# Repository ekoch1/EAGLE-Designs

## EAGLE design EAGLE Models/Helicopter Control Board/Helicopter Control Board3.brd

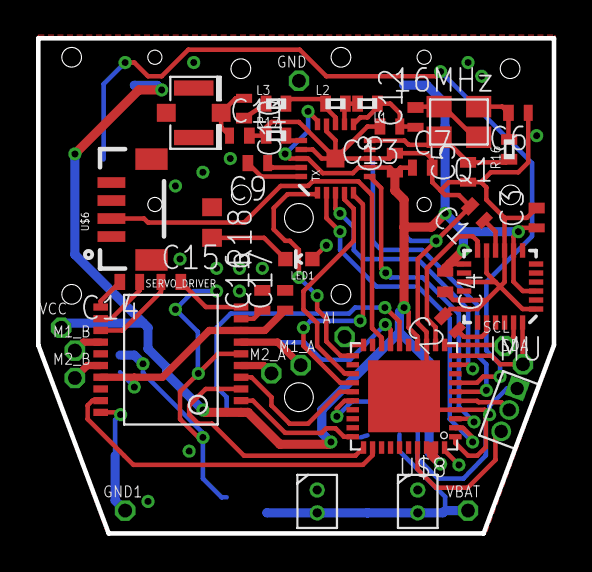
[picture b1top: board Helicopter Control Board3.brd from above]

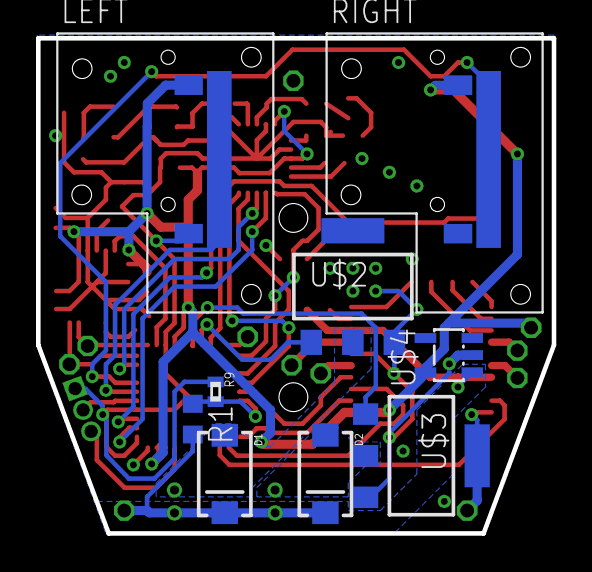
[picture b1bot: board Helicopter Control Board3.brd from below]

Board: 2 copper layers, 28.7 x 27.5 mm, 54 parts (9 on the bottom side), 49 nets.

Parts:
AI: LSP10
C1, C3, C14, C15, C16, C17: .1uF; C0402
C2, C12: 2.2nF; C0402
C4, C8: 10nF; C0402
C5, C6: 22pF; C0402
C7: 1nF; C0402
C9: 33nF; C0402
C10: 1.5pF; C0402
C11: 1pF; C0402
C13: 4.7pF; C0402
D1, D2: SMA-DIODE
GND, GND1: LSP10
IMU: QFN-24-NP
J2: U.FL
L1: 2.7nH; R0402
L2: 8.2nH; R0402
L3: 3.9nH; R0402
LED1: LED-0603
LEFT: SURF_POT
M1_A, M1_B, M2_A, M2_B: LSP10
MTR0, MTR1: MOTOR_CONN
PRGM: HEADER_3_0.05; HEADER_3_.05
Q1: 16MHz; TXC-4SMD
R1: 10k; R0603
R9: 10k; R0402
R16: 1M; R0402
R17: 22k; R0402
R18: 50; R0603
RIGHT: SURF_POT
SCL: LSP10
SDA: LSP10
SERVO_DRIVER: MPC17531A; SSOP_20
TX: NRF24L01SMD; QFN20
U$2, U$3: BSP75N; PG-SOT-223
U$4: LP5907_2.8V; SOT23-DBV
U$6: JST_4_VERTICAL; JST-4-SMD-VERT-1.0MM
U$8: G2955IRHA40R; RHA40
VBAT: LSP10
VCC: LSP10

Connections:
A7: R1.1, R9.2, U$8.26
AI: AI.MP, LED1.A, U$8.20
BODY_LED: U$6.2, U$8.18
B_MTR0: U$3.1, U$8.16
B_MTR1: U$2.1, U$8.17
CE: TX.1, U$8.21
CSN: TX.2, U$8.2
GND: C1.2, C2.2, C3.2, C4.2, C5.1, C6.1, C7.2, C8.2, C9.2, C11.2, C12.2, C13.2, C16.2, C17.2, GND.MP, GND1.MP, IMU.1, IMU.9, IMU.11, IMU.15, IMU.17, IMU.18, J2.P$1, J2.P$2, LEFT.LO, PRGM.P$1, Q1.P2, Q1.P4, R9.1, R17.1, R18.1, RIGHT.LO, SERVO_DRIVER.6, SERVO_DRIVER.15, SERVO_DRIVER.20, TX.0, TX.8, TX.14, TX.17, TX.20, U$2.3, U$2.4, U$3.3, U$3.4, U$4.2, U$6.3, U$6.4, U$8.1, U$8.4, U$8.13, U$8.TP
IRQ: TX.6, U$8.3
LEFT_POT_OUT: LEFT.OUT, U$8.6
M1_CTRLA: SERVO_DRIVER.2, U$8.30
M1_CTRLB: SERVO_DRIVER.3, U$8.31
M2_CTRLA: SERVO_DRIVER.19, U$8.32
M2_CTRLB: SERVO_DRIVER.18, U$8.40
MISO: TX.5, U$8.24
MOSI: TX.4, U$8.23
unnamed: M1_A.MP, SERVO_DRIVER.7
unnamed: M1_B.MP, SERVO_DRIVER.14
unnamed: M2_A.MP, SERVO_DRIVER.5
unnamed: IMU.12, U$8.12
unnamed: C1.1, IMU.10
unnamed: C2.1, IMU.20
unnamed: M2_B.MP, SERVO_DRIVER.16
unnamed: C14.1, SERVO_DRIVER.12
unnamed: C14.2, SERVO_DRIVER.11
unnamed: C15.1, SERVO_DRIVER.13
unnamed: C10.2, L3.1
unnamed: D1.A, MTR1.P$1, U$2.2
unnamed: D2.A, MTR0.P$1, U$3.2
unnamed: C6.2, Q1.P1, R16.2, TX.9
unnamed: C5.2, Q1.P3, R16.1, TX.10
unnamed: C9.1, TX.19
unnamed: R17.2, TX.16
unnamed: L1.2, L2.2, TX.12
unnamed: C12.1, C13.1, L1.1, TX.11
unnamed: L2.1, L3.2, TX.13
unnamed: C10.1, C11.1, J2.P$3
unnamed: C15.2, SERVO_DRIVER.10
unnamed: LED1.C, R18.2
unnamed: C16.1, SERVO_DRIVER.9
PSAVE: SERVO_DRIVER.4, U$8.25
RIGHT_POT_OUT: RIGHT.OUT, U$8.7
RST: PRGM.P$2, U$8.5
SCK: TX.3, U$8.9
SCL: IMU.23, SCL.MP, U$8.11
SDA: IMU.24, SDA.MP, U$8.10
TEST: PRGM.P$3, U$8.37
VBAT: C17.1, D1.C, D2.C, MTR0.P$2, MTR1.P$2, R1.2, SERVO_DRIVER.8, SERVO_DRIVER.17, U$4.1, U$4.3, VBAT.MP
VCC: C3.1, C4.1, C7.1, C8.1, IMU.3, IMU.8, IMU.13, LEFT.HI, RIGHT.HI, SERVO_DRIVER.1, TX.7, TX.15, TX.18, U$4.5, U$8.14, U$8.38, U$8.39, VCC.MP

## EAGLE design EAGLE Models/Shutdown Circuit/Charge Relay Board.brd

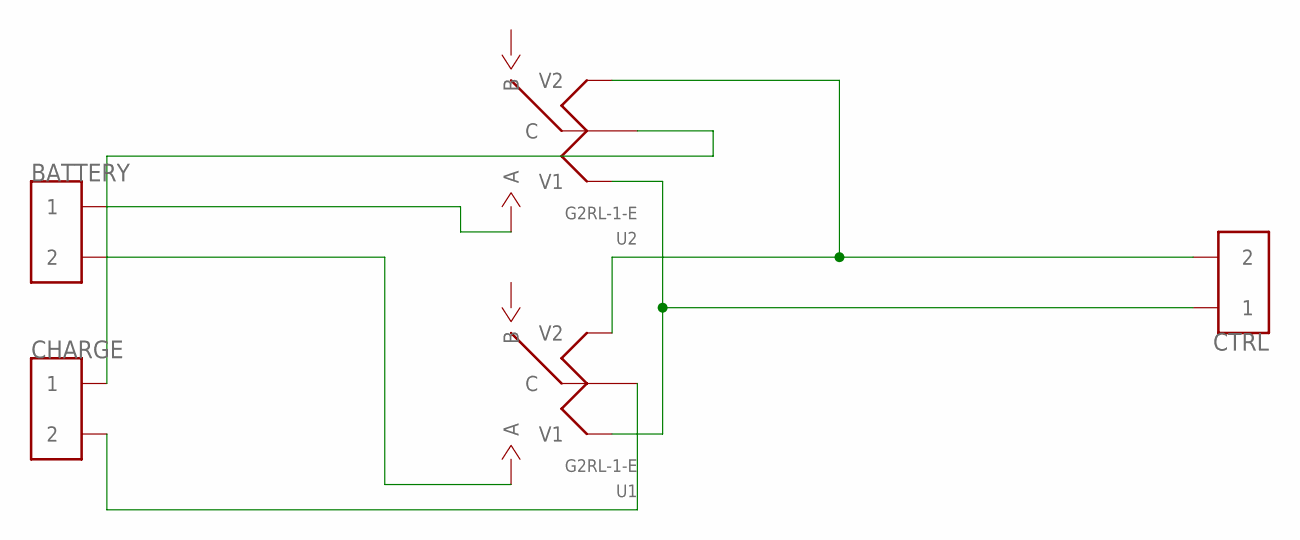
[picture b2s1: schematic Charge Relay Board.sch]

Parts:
BATTERY: CONN_2; CONNECTOR_2
CHARGE: CONN_2; CONNECTOR_2
CTRL: CONN_2; CONNECTOR_2
U1, U2: G2RL-1-E; G2RL-1-E_RELAY

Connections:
unnamed: CTRL.3 (2), CTRL.4 (2), U1.P$8 (V2), U2.P$8 (V2)
unnamed: CTRL.1, CTRL.2 (1), U1.P$1 (V1), U2.P$1 (V1)
unnamed: BATTERY.1, BATTERY.2 (1), U2.P$4 (A), U2.P$5 (A)
unnamed: BATTERY.3 (2), BATTERY.4 (2), U1.P$4 (A), U1.P$5 (A)
unnamed: CHARGE.1, CHARGE.2 (1), U2.P$3 (C), U2.P$6 (C)
unnamed: CHARGE.3 (2), CHARGE.4 (2), U1.P$3 (C), U1.P$6 (C)

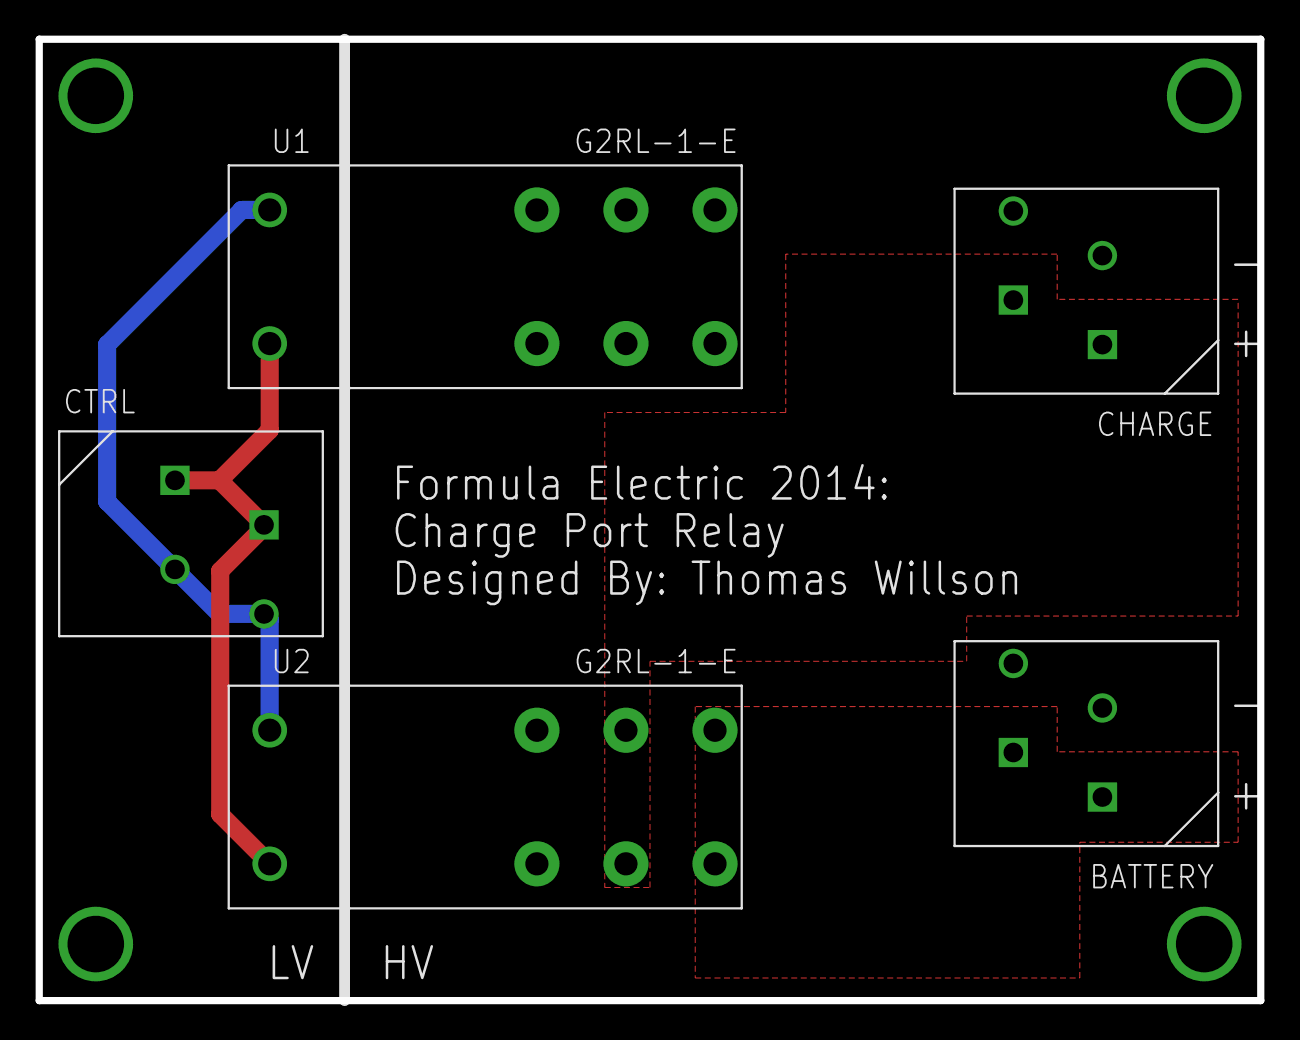
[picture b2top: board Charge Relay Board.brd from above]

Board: 2 copper layers, 68.6 x 54.0 mm, 5 parts (0 on the bottom side), 6 nets.

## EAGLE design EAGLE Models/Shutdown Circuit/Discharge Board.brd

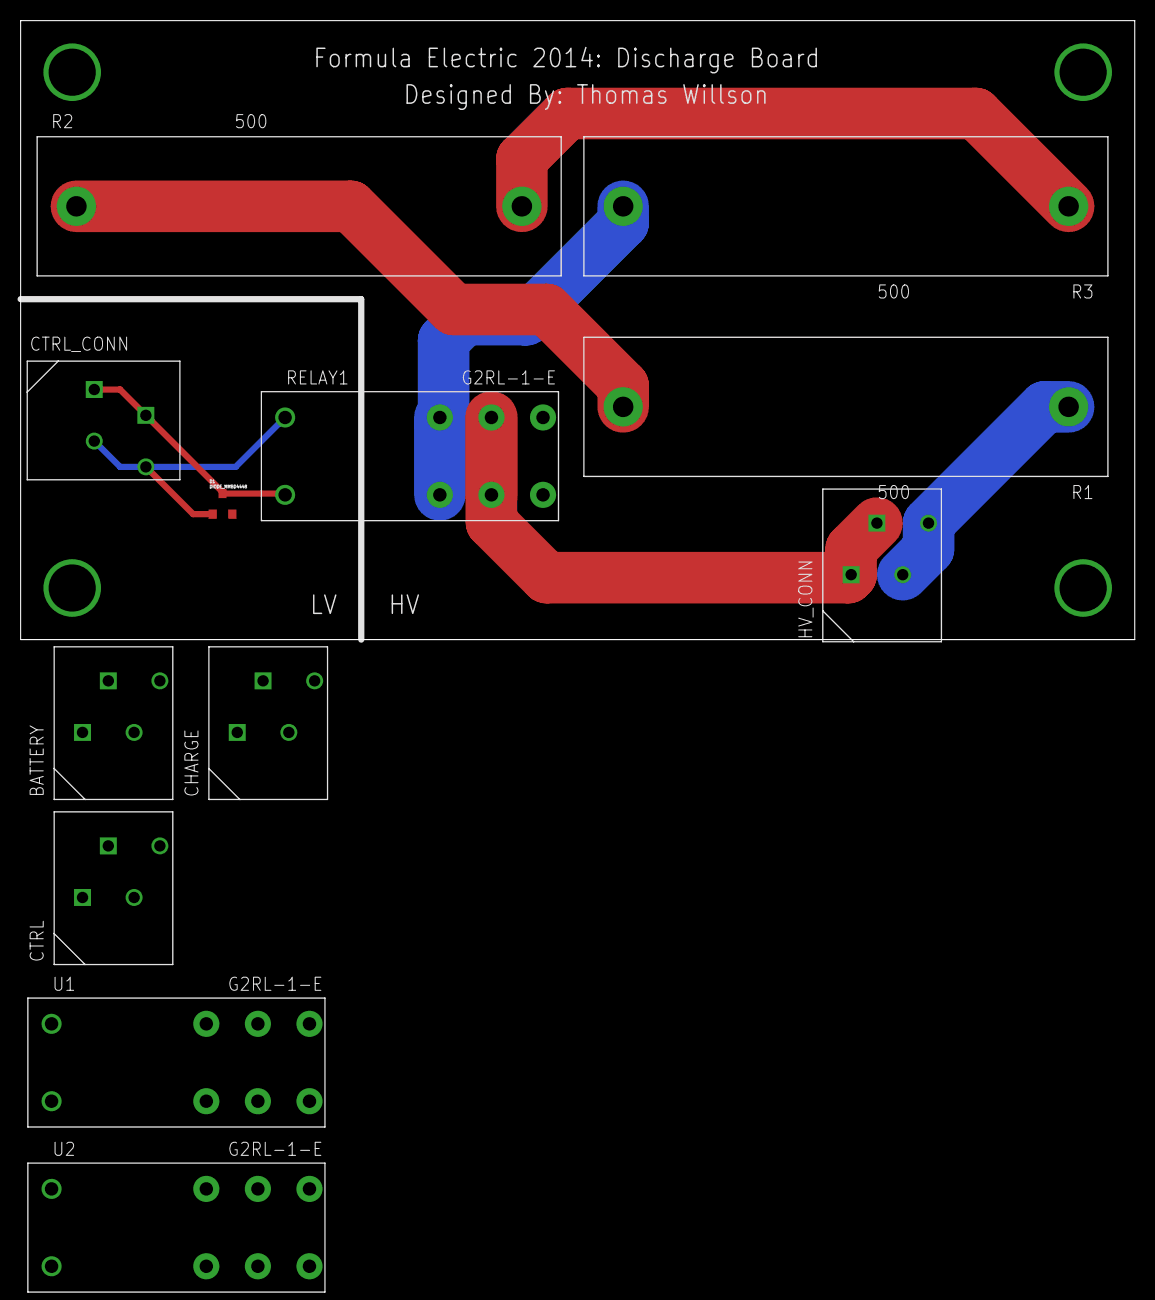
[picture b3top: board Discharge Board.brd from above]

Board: 2 copper layers, 108.0 x 60.0 mm, 12 parts (0 on the bottom side), 13 nets.

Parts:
BATTERY: CONN_2; CONNECTOR_2
CHARGE: CONN_2; CONNECTOR_2
CTRL: CONN_2; CONNECTOR_2
CTRL_CONN: CONN_2; CONNECTOR_2
D1: DIODE_MMBD4448; SOT-23-3
HV_CONN: CONN_2; CONNECTOR_2
R1, R2, R3: 500; VISHAY_FS20W_RES
RELAY1: G2RL-1-E; G2RL-1-E_RELAY
U1, U2: G2RL-1-E; G2RL-1-E_RELAY

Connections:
GND: CTRL_CONN.3, CTRL_CONN.4, D1.P$2, RELAY1.P$8
unnamed: CTRL.3, CTRL.4, U1.P$8, U2.P$8
unnamed: CTRL.1, CTRL.2, U1.P$1, U2.P$1
unnamed: R3.P$2, RELAY1.P$2, RELAY1.P$7
unnamed: HV_CONN.1, HV_CONN.2, RELAY1.P$3, RELAY1.P$6
unnamed: HV_CONN.3, HV_CONN.4, R1.P$1
unnamed: R1.P$2, R2.P$1
unnamed: R2.P$2, R3.P$1
unnamed: BATTERY.1, BATTERY.2, U2.P$4, U2.P$5
unnamed: BATTERY.3, BATTERY.4, U1.P$4, U1.P$5
unnamed: CHARGE.1, CHARGE.2, U2.P$3, U2.P$6
unnamed: CHARGE.3, CHARGE.4, U1.P$3, U1.P$6
TSMS_IN: CTRL_CONN.1, CTRL_CONN.2, D1.P$1, RELAY1.P$1

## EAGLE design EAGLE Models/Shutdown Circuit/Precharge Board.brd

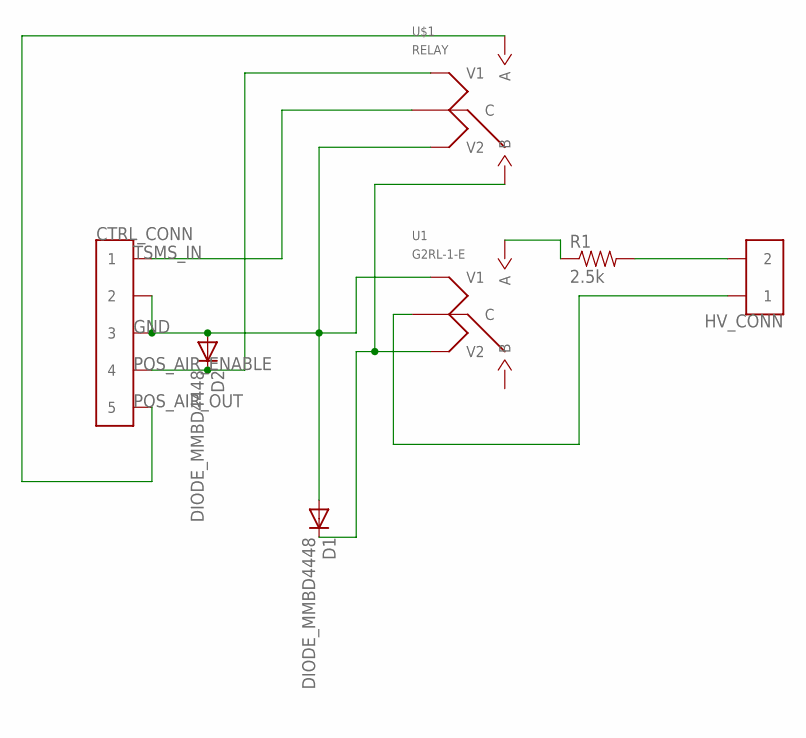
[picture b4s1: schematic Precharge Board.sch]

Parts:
CTRL_CONN: CONN_5; CONNECTOR_5
D1, D2: DIODE_MMBD4448; SOT-23-3
HV_CONN: CONN_2; CONNECTOR_2
R1: 2.5k; VISHAY_FS20W_RES
U1: G2RL-1-E; G2RL-1-E_RELAY
U$1: RELAY

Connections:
GND: CTRL_CONN.3 (2), CTRL_CONN.4 (2), CTRL_CONN.5 (3), CTRL_CONN.6 (3), D1.P$2 (A), D2.P$2 (A), U1.P$1 (V1), U$1.V2
unnamed: HV_CONN.3 (2), HV_CONN.4 (2), R1.P$2 (2)
unnamed: HV_CONN.1, HV_CONN.2 (1), U1.P$3 (C), U1.P$6 (C)
unnamed: D1.P$1 (C), U1.P$8 (V2), U$1.B
unnamed: R1.P$1 (1), U1.P$4 (A), U1.P$5 (A)
POS_AIR_ENABLE: CTRL_CONN.7 (4), CTRL_CONN.8 (4), D2.P$1 (C), U$1.V1
POS_AIR_OUT: CTRL_CONN.9 (5), CTRL_CONN.10 (5), U$1.A
TSMS_IN: CTRL_CONN.1, CTRL_CONN.2 (1), U$1.CENTER (C)

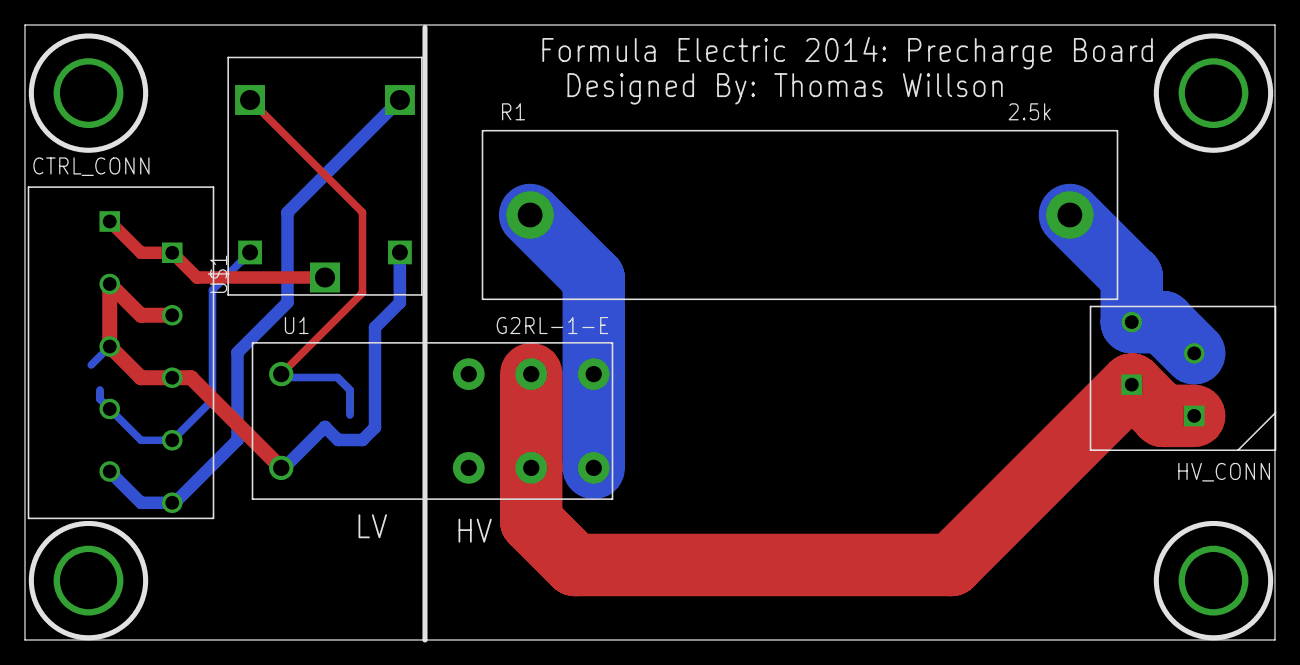
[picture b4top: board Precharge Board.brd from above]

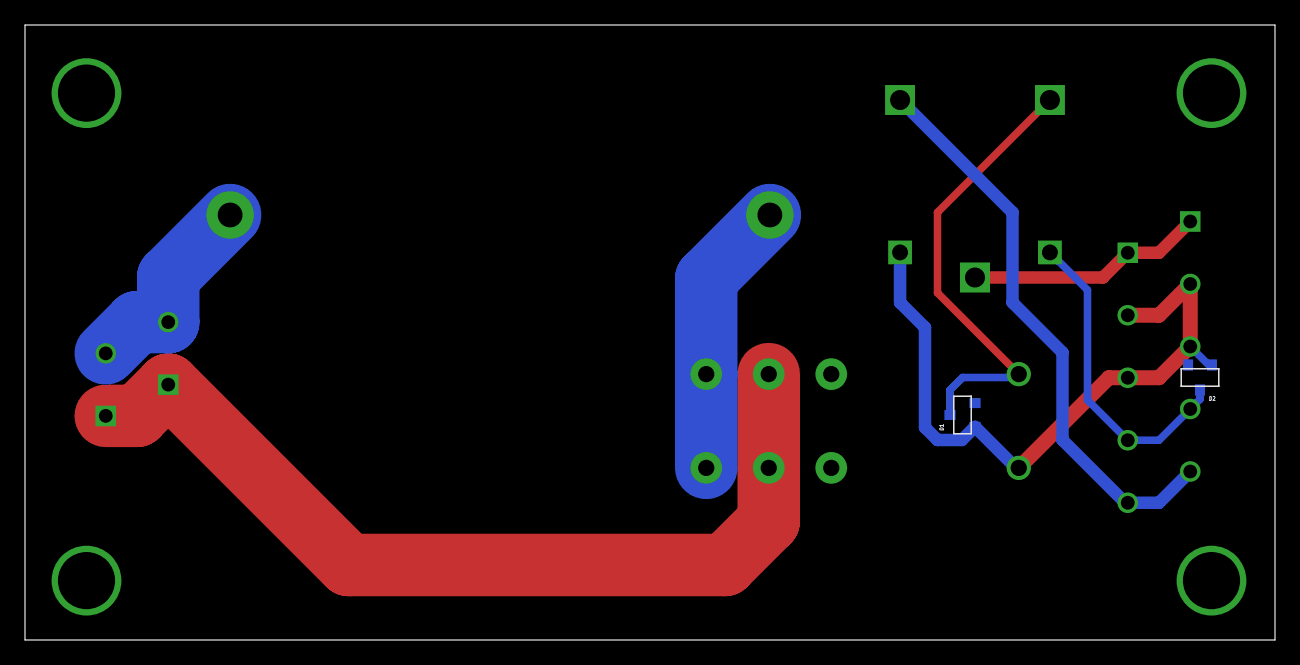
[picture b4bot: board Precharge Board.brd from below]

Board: 2 copper layers, 100.0 x 49.2 mm, 7 parts (2 on the bottom side), 8 nets.

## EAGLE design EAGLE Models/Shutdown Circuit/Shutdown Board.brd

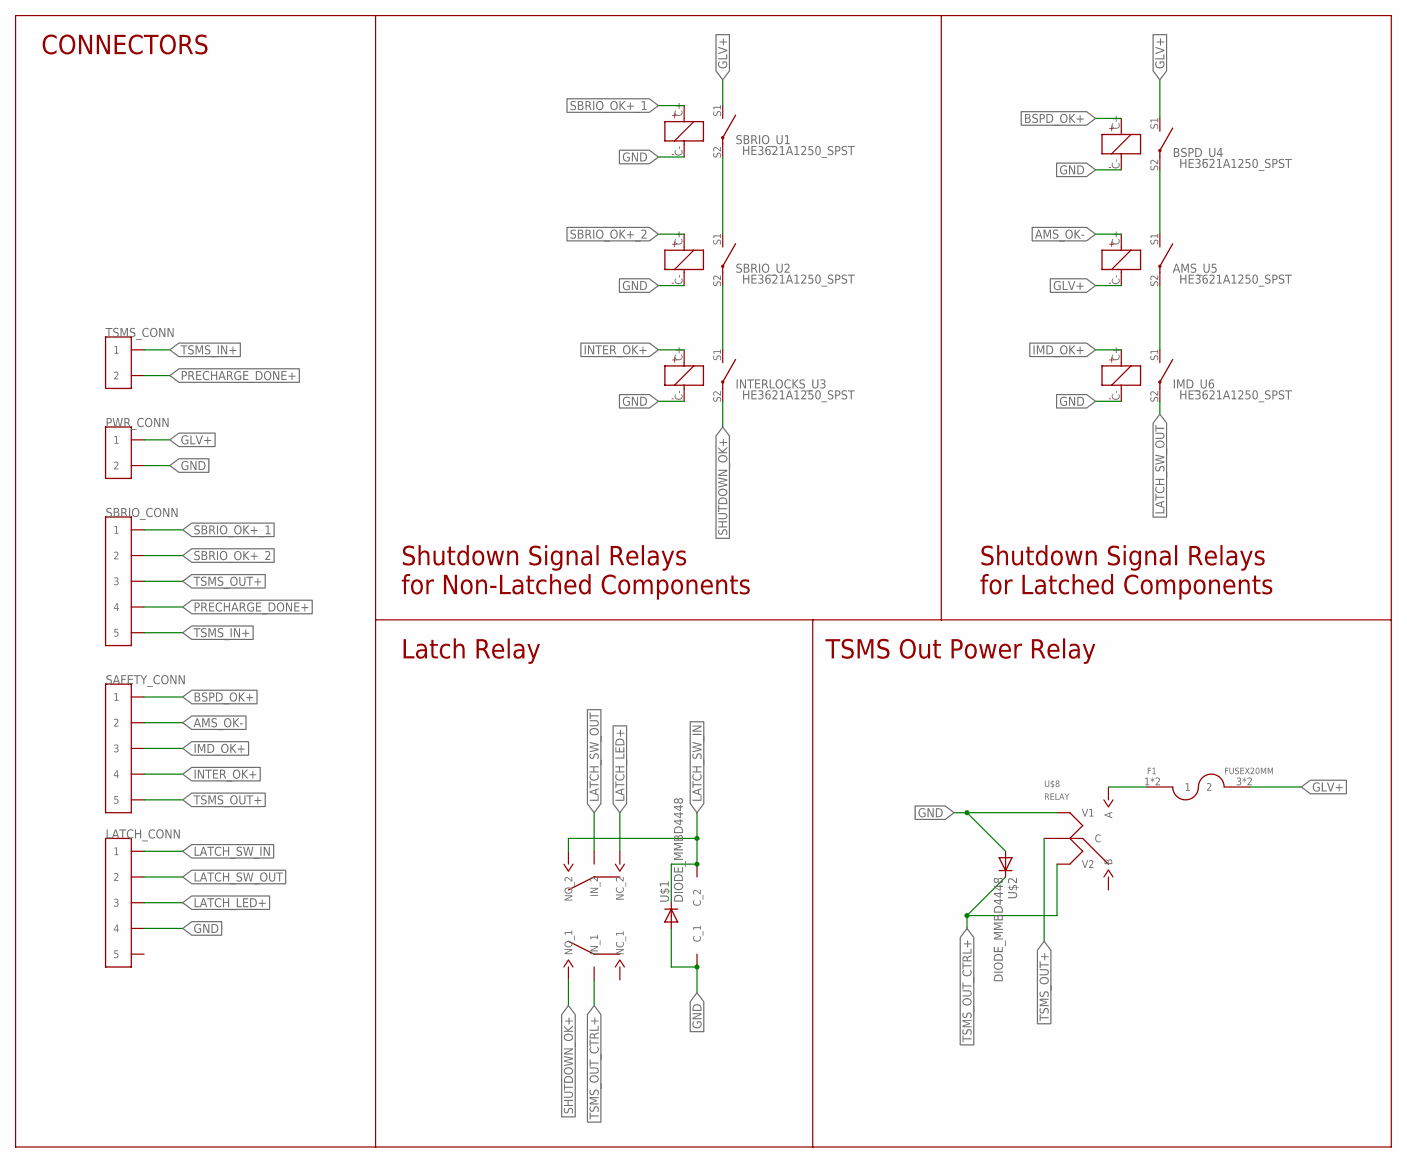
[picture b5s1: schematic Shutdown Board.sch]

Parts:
AMS_U5: HE3621A1250_SPST
BSPD_U4: HE3621A1250_SPST
F1: FUSEX20MM; FUSE_5MM
IMD_U6: HE3621A1250_SPST
INTERLOCKS_U3: HE3621A1250_SPST
LATCH_CONN: CONN_5; CONNECTOR_5
LATCH_U7: JW2SN-DC12V; DPDT_JW2_FORM_C
PWR_CONN: CONN_2; CONNECTOR_2
SAFETY_CONN: CONN_5; CONNECTOR_5
SBRIO_CONN: CONN_5; CONNECTOR_5
SBRIO_U1, SBRIO_U2: HE3621A1250_SPST
TSMS_CONN: CONN_2; CONNECTOR_2
U$1, U$2: DIODE_MMBD4448; SOT-23-3
U$8: RELAY

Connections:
AMS_OK-: AMS_U5.C+, SAFETY_CONN.3 (2), SAFETY_CONN.4 (2)
BSPD_OK+: BSPD_U4.C+, SAFETY_CONN.1, SAFETY_CONN.2 (1)
GLV+: AMS_U5.C-, BSPD_U4.S1 (SW_1), F1.3 (2), F1.4 (2), PWR_CONN.1, PWR_CONN.2 (1), SBRIO_U1.S1 (SW_1)
GND: BSPD_U4.C-, IMD_U6.C-, INTERLOCKS_U3.C-, LATCH_CONN.7 (4), LATCH_CONN.8 (4), LATCH_U7.COIL_1 (C_1), PWR_CONN.3 (2), PWR_CONN.4 (2), SBRIO_U1.C-, SBRIO_U2.C-, U$1.P$2 (A), U$2.P$2 (A), U$8.V1
IMD_OK+: IMD_U6.C+, SAFETY_CONN.5 (3), SAFETY_CONN.6 (3)
INTER_OK+: INTERLOCKS_U3.C+, SAFETY_CONN.7 (4), SAFETY_CONN.8 (4)
LATCH_LED+: LATCH_CONN.5 (3), LATCH_CONN.6 (3), LATCH_U7.NC_2
LATCH_SW_IN: LATCH_CONN.1, LATCH_CONN.2 (1), LATCH_U7.COIL_2 (C_2), LATCH_U7.NO_2, U$1.P$1 (C)
LATCH_SW_OUT: IMD_U6.S2 (SW_2), LATCH_CONN.3 (2), LATCH_CONN.4 (2), LATCH_U7.CENTER_2 (IN_2)
unnamed: SBRIO_U1.S2 (SW_2), SBRIO_U2.S1 (SW_1)
unnamed: INTERLOCKS_U3.S1 (SW_1), SBRIO_U2.S2 (SW_2)
unnamed: AMS_U5.S1 (SW_1), BSPD_U4.S2 (SW_2)
unnamed: AMS_U5.S2 (SW_2), IMD_U6.S1 (SW_1)
unnamed: F1.1, F1.2 (1), U$8.A
PRECHARGE_DONE+: SBRIO_CONN.7 (4), SBRIO_CONN.8 (4), TSMS_CONN.3 (2), TSMS_CONN.4 (2)
SBRIO_OK+_1: SBRIO_CONN.1, SBRIO_CONN.2 (1), SBRIO_U1.C+
SBRIO_OK+_2: SBRIO_CONN.3 (2), SBRIO_CONN.4 (2), SBRIO_U2.C+
SHUTDOWN_OK+: INTERLOCKS_U3.S2 (SW_2), LATCH_U7.NO_1
TSMS_IN+: SBRIO_CONN.9 (5), SBRIO_CONN.10 (5), TSMS_CONN.1, TSMS_CONN.2 (1)
TSMS_OUT+: SAFETY_CONN.9 (5), SAFETY_CONN.10 (5), SBRIO_CONN.5 (3), SBRIO_CONN.6 (3), U$8.CENTER (C)
TSMS_OUT_CTRL+: LATCH_U7.CENTER_1 (IN_1), U$2.P$1 (C), U$8.V2

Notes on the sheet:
CONNECTORS
Shutdown Signal Relays for Non-Latched Components
Shutdown Signal Relays for Latched Components
Latch Relay
TSMS Out Power Relay

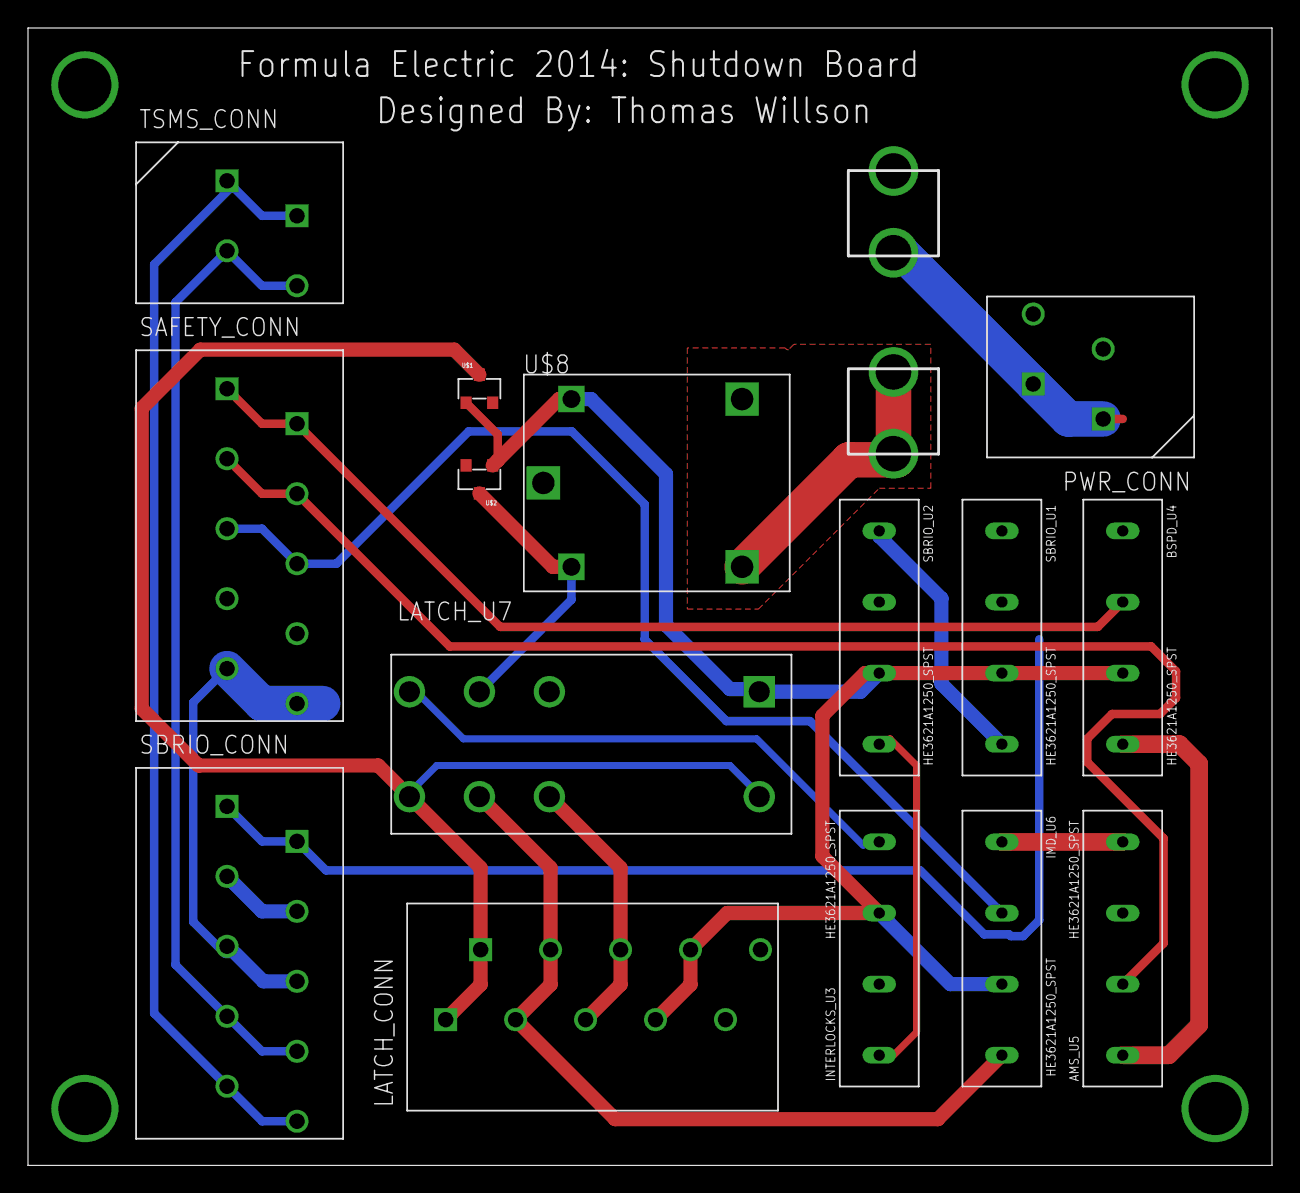
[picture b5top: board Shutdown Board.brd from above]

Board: 2 copper layers, 88.9 x 81.3 mm, 16 parts (0 on the bottom side), 21 nets.

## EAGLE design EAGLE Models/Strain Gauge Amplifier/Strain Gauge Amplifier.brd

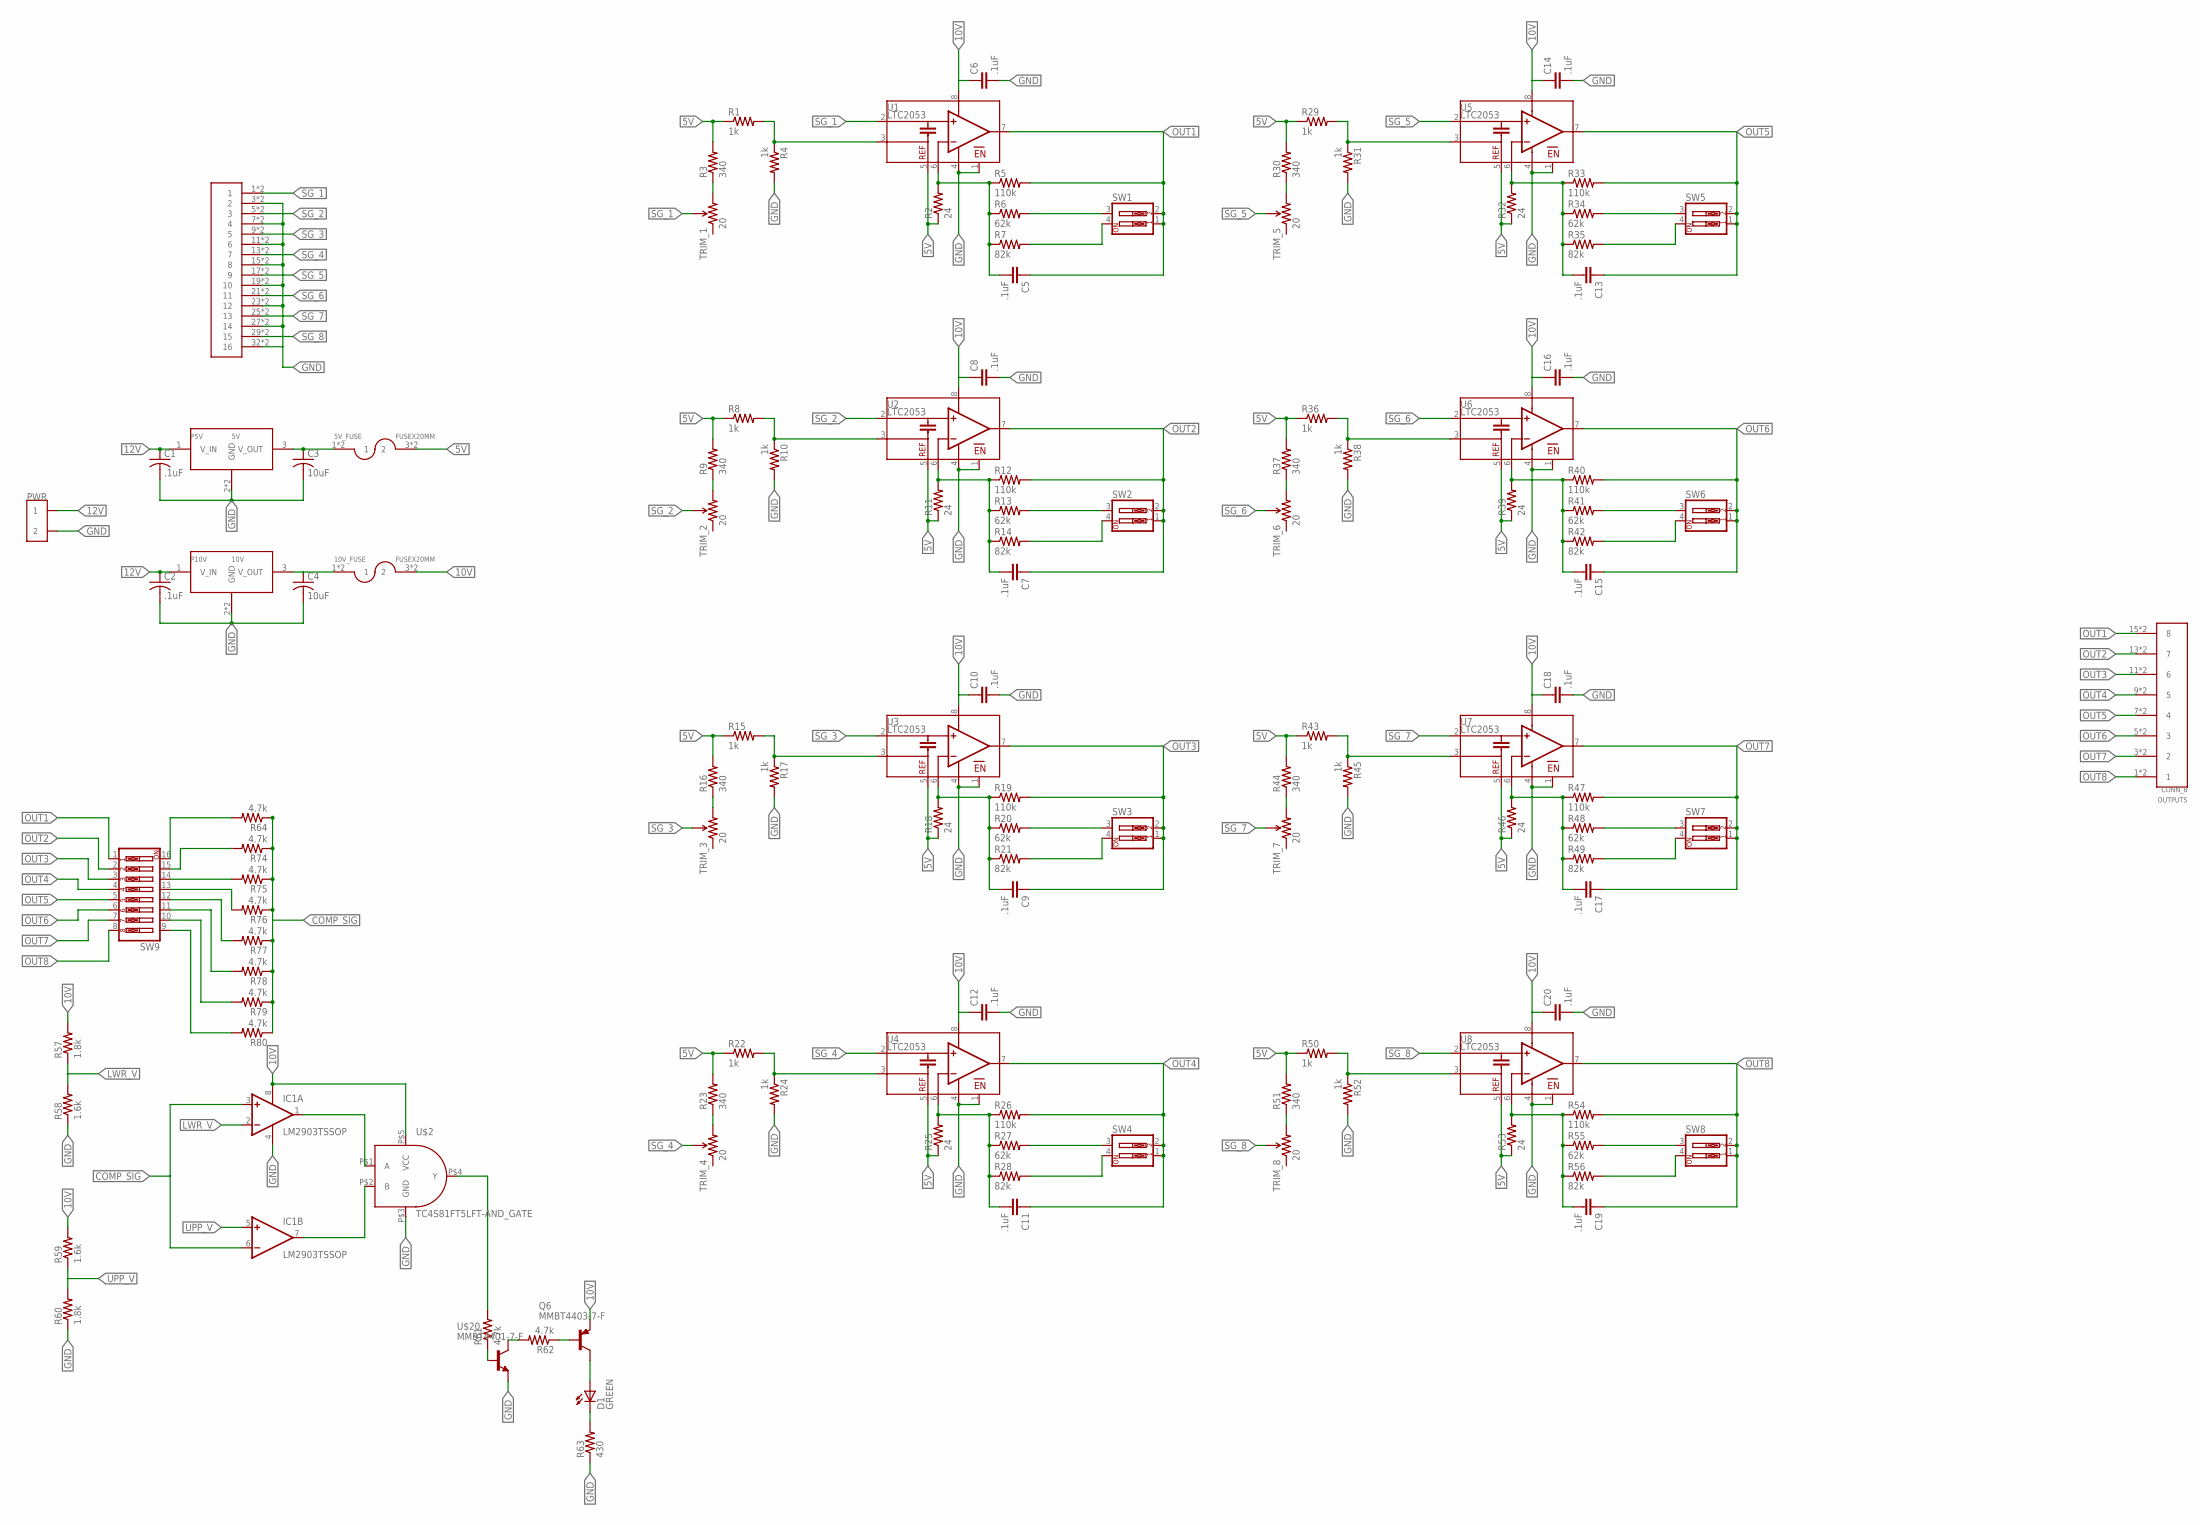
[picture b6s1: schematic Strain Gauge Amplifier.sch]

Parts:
5V_FUSE, 10V_FUSE: FUSEX20MM; FUSE_5MM
C1, C2: .1uF; C0603
C3, C4: 10uF; C1206
C5, C6, C7, C8, C9, C10, C11, C12, C13, C14, C15, C16, C17, C18, C19, C20: .1uF; 0603-CAP
D1: GREEN; LED-0603
IC1: LM2903TSSOP; TSSOP8
OUTPUTS: CONN_8; CONNECTOR_8
P5V: 5V; SOT223
P10V: 10V; SOT223
PWR: CONN_2; CONNECTOR_2
Q6: MMBT4403-7-F; SOT-23-3
R1, R4, R8, R10, R15, R17, R22, R24, R29, R31, R36, R38, R43, R45, R50, R52: 1k; 0603-RES
R2, R11, R18, R25, R32, R39, R46, R53: 24; 0603-RES
R3, R9, R16, R23, R30, R37, R44, R51: 340; 0603-RES
R5, R12, R19, R26, R33, R40, R47, R54: 110k; 0603-RES
R6, R13, R20, R27, R34, R41, R48, R55: 62k; 0603-RES
R7, R14, R21, R28, R35, R42, R49, R56: 82k; 0603-RES
R57, R60: 1.8k; 0603-RES
R58, R59: 1.6k; 0603-RES
R61, R62, R64, R74, R75, R76, R77, R78, R79, R80: 4.7k; 0603-RES
R63: 430; 0603-RES
SG_CONN: CONN_16; CONNECTOR_16
SW1, SW2, SW3, SW4, SW5, SW6, SW7, SW8: SW_DIP-2; DIPSWITCH-02
SW9: SW_DIP-8; DIPSWITCH-08
TRIM_1, TRIM_2, TRIM_3, TRIM_4, TRIM_5, TRIM_6, TRIM_7, TRIM_8: 20; 3926_Y,Z
U1, U2, U3, U4, U5, U6, U7, U8: LTC2053; MSOP8
U$2: TC4S81FT5LFT-AND_GATE; SSOP5-P-0.95
U$20: MMBT4401-7-F; SOT-23-3

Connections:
5V: 5V_FUSE.3 (2), 5V_FUSE.4 (2), R1.1, R2.1, R3.2, R8.1, R9.2, R11.1, R15.1, R16.2, R18.1, R22.1, R23.2, R25.1, R29.1, R30.2, R32.1, R36.1, R37.2, R39.1, R43.1, R44.2, R46.1, R50.1, R51.2, R53.1, U1.5 (REF), U2.5 (REF), U3.5 (REF), U4.5 (REF), U5.5 (REF), U6.5 (REF), U7.5 (REF), U8.5 (REF)
10V: 10V_FUSE.3 (2), 10V_FUSE.4 (2), C6.1, C8.1, C10.1, C12.1, C14.1, C16.1, C18.1, C20.1, IC1.8 (V+), Q6.P$3 (E), R57.2, R59.2, U1.8 (V+), U2.8 (V+), U3.8 (V+), U4.8 (V+), U5.8 (V+), U6.8 (V+), U7.8 (V+), U8.8 (V+), U$2.P$5 (VCC)
12V: C1.1, C2.1, P5V.1 (V_IN), P10V.1 (V_IN), PWR.1, PWR.2 (1)
COMP_SIG: IC1.3 (+IN), IC1.6 (-IN), R64.1, R74.1, R75.1, R76.1, R77.1, R78.1, R79.1, R80.1
GND: C1.2, C2.2, C3.2, C4.2, C6.2, C8.2, C10.2, C12.2, C14.2, C16.2, C18.2, C20.2, IC1.4 (V-), P5V.2 (GND), P5V.4 (GND), P10V.2 (GND), P10V.4 (GND), PWR.3 (2), PWR.4 (2), R4.2, R10.2, R17.2, R24.2, R31.2, R38.2, R45.2, R52.2, R58.1, R60.1, R63.1, SG_CONN.3 (2), SG_CONN.4 (2), SG_CONN.7 (4), SG_CONN.8 (4), SG_CONN.11 (6), SG_CONN.12 (6), SG_CONN.15 (8), SG_CONN.16 (8), SG_CONN.19 (10), SG_CONN.20 (10), SG_CONN.23 (12), SG_CONN.24 (12), SG_CONN.27 (14), SG_CONN.28 (14), SG_CONN.32 (16), SG_CONN.P31 (16), U1.1 (EN), U1.4 (V-), U2.1 (EN), U2.4 (V-), U3.1 (EN), U3.4 (V-), U4.1 (EN), U4.4 (V-), U5.1 (EN), U5.4 (V-), U6.1 (EN), U6.4 (V-), U7.1 (EN), U7.4 (V-), U8.1 (EN), U8.4 (V-), U$2.P$3 (GND), U$20.P$3 (E)
LWR_V: IC1.2 (-IN), R57.1, R58.2
unnamed: C5.2, R2.2, R5.1, R6.1, R7.1, U1.6 (RG)
unnamed: 5V_FUSE.1, 5V_FUSE.2 (1), C3.1, P5V.3 (V_OUT)
unnamed: 10V_FUSE.1, 10V_FUSE.2 (1), C4.1, P10V.3 (V_OUT)
unnamed: R1.2, R4.1, U1.3 (+IN)
unnamed: IC1.1 (OUT), U$2.P$1 (A)
unnamed: R3.1, TRIM_1.3 (CW)
unnamed: R6.2, SW1.3
unnamed: R7.2, SW1.4
unnamed: R8.2, R10.1, U2.3 (+IN)
unnamed: C7.2, R11.2, R12.1, R13.1, R14.1, U2.6 (RG)
unnamed: IC1.7 (OUT), U$2.P$2 (B)
unnamed: R9.1, TRIM_2.3 (CW)
unnamed: R13.2, SW2.3
unnamed: R14.2, SW2.4
unnamed: R15.2, R17.1, U3.3 (+IN)
unnamed: C9.2, R18.2, R19.1, R20.1, R21.1, U3.6 (RG)
unnamed: R61.1, U$20.P$2 (B)
unnamed: R16.1, TRIM_3.3 (CW)
unnamed: R20.2, SW3.3
unnamed: R21.2, SW3.4
unnamed: R22.2, R24.1, U4.3 (+IN)
unnamed: C11.2, R25.2, R26.1, R27.1, R28.1, U4.6 (RG)
unnamed: R62.2, U$20.P$1 (C)
unnamed: R23.1, TRIM_4.3 (CW)
unnamed: R27.2, SW4.3
unnamed: R28.2, SW4.4
unnamed: R29.2, R31.1, U5.3 (+IN)
unnamed: C13.2, R32.2, R33.1, R34.1, R35.1, U5.6 (RG)
unnamed: Q6.P$2 (B), R62.1
unnamed: R30.1, TRIM_5.3 (CW)
unnamed: R34.2, SW5.3
unnamed: R35.2, SW5.4
unnamed: R36.2, R38.1, U6.3 (+IN)
unnamed: C15.2, R39.2, R40.1, R41.1, R42.1, U6.6 (RG)
unnamed: R61.2, U$2.P$4 (Y)
unnamed: R37.1, TRIM_6.3 (CW)
unnamed: R41.2, SW6.3
unnamed: R42.2, SW6.4
unnamed: R43.2, R45.1, U7.3 (+IN)
unnamed: C17.2, R46.2, R47.1, R48.1, R49.1, U7.6 (RG)
unnamed: D1.A, Q6.P$1 (C)
unnamed: R44.1, TRIM_7.3 (CW)
unnamed: R48.2, SW7.3
unnamed: R49.2, SW7.4
unnamed: R50.2, R52.1, U8.3 (+IN)
unnamed: C19.2, R53.2, R54.1, R55.1, R56.1, U8.6 (RG)
unnamed: D1.C, R63.2
unnamed: R51.1, TRIM_8.3 (CW)
unnamed: R55.2, SW8.3
unnamed: R56.2, SW8.4
unnamed: R64.2, SW9.16
unnamed: R74.2, SW9.15
unnamed: R75.2, SW9.14
unnamed: R76.2, SW9.13
unnamed: R77.2, SW9.12
unnamed: R78.2, SW9.11
unnamed: R79.2, SW9.10
unnamed: R80.2, SW9.9
OUT1: C5.1, OUTPUTS.15 (8), OUTPUTS.16 (8), R5.2, SW1.1, SW1.2, SW9.1, U1.7 (OUT)
OUT2: C7.1, OUTPUTS.13 (7), OUTPUTS.14 (7), R12.2, SW2.1, SW2.2, SW9.2, U2.7 (OUT)
OUT3: C9.1, OUTPUTS.11 (6), OUTPUTS.12 (6), R19.2, SW3.1, SW3.2, SW9.3, U3.7 (OUT)
OUT4: C11.1, OUTPUTS.9 (5), OUTPUTS.10 (5), R26.2, SW4.1, SW4.2, SW9.4, U4.7 (OUT)
OUT5: C13.1, OUTPUTS.7 (4), OUTPUTS.8 (4), R33.2, SW5.1, SW5.2, SW9.5, U5.7 (OUT)
OUT6: C15.1, OUTPUTS.5 (3), OUTPUTS.6 (3), R40.2, SW6.1, SW6.2, SW9.6, U6.7 (OUT)
OUT7: C17.1, OUTPUTS.3 (2), OUTPUTS.4 (2), R47.2, SW7.1, SW7.2, SW9.7, U7.7 (OUT)
OUT8: C19.1, OUTPUTS.1, OUTPUTS.2 (1), R54.2, SW8.1, SW8.2, SW9.8, U8.7 (OUT)
SG_1: SG_CONN.1, SG_CONN.2 (1), TRIM_1.2 (WIPER), U1.2 (-IN)
SG_2: SG_CONN.5 (3), SG_CONN.6 (3), TRIM_2.2 (WIPER), U2.2 (-IN)
SG_3: SG_CONN.9 (5), SG_CONN.10 (5), TRIM_3.2 (WIPER), U3.2 (-IN)
SG_4: SG_CONN.13 (7), SG_CONN.14 (7), TRIM_4.2 (WIPER), U4.2 (-IN)
SG_5: SG_CONN.17 (9), SG_CONN.18 (9), TRIM_5.2 (WIPER), U5.2 (-IN)
SG_6: SG_CONN.21 (11), SG_CONN.22 (11), TRIM_6.2 (WIPER), U6.2 (-IN)
SG_7: SG_CONN.25 (13), SG_CONN.26 (13), TRIM_7.2 (WIPER), U7.2 (-IN)
SG_8: SG_CONN.29 (15), SG_CONN.30 (15), TRIM_8.2 (WIPER), U8.2 (-IN)
UPP_V: IC1.5 (+IN), R59.1, R60.2

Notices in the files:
parts and their libraries:
SparkFun-Sensors: Licensing: CC v3.0 Share-Alike You are welcome to use this library for commercial purposes.
